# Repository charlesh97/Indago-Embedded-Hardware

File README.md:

# Indago-Embedded-HW

Archived project.

See latest
[PCB](https://gitlab.com/indago-smart-tracker/indago-embedded-hw/-/blob/main/Hardware/v5_Miniature/Main%20Design%20B/Tracker_v5BPCB.pdf),
[Schematic](https://gitlab.com/indago-smart-tracker/indago-embedded-hw/-/blob/main/Hardware/v5_Miniature/Main%20Design%20B/Tracker_v5BSCH.pdf),
[Staged Product Rendering](https://gitlab.com/indago-smart-tracker/indago-embedded-hw/-/blob/main/Renderings/AssetTracker_TestProductMockup.png)

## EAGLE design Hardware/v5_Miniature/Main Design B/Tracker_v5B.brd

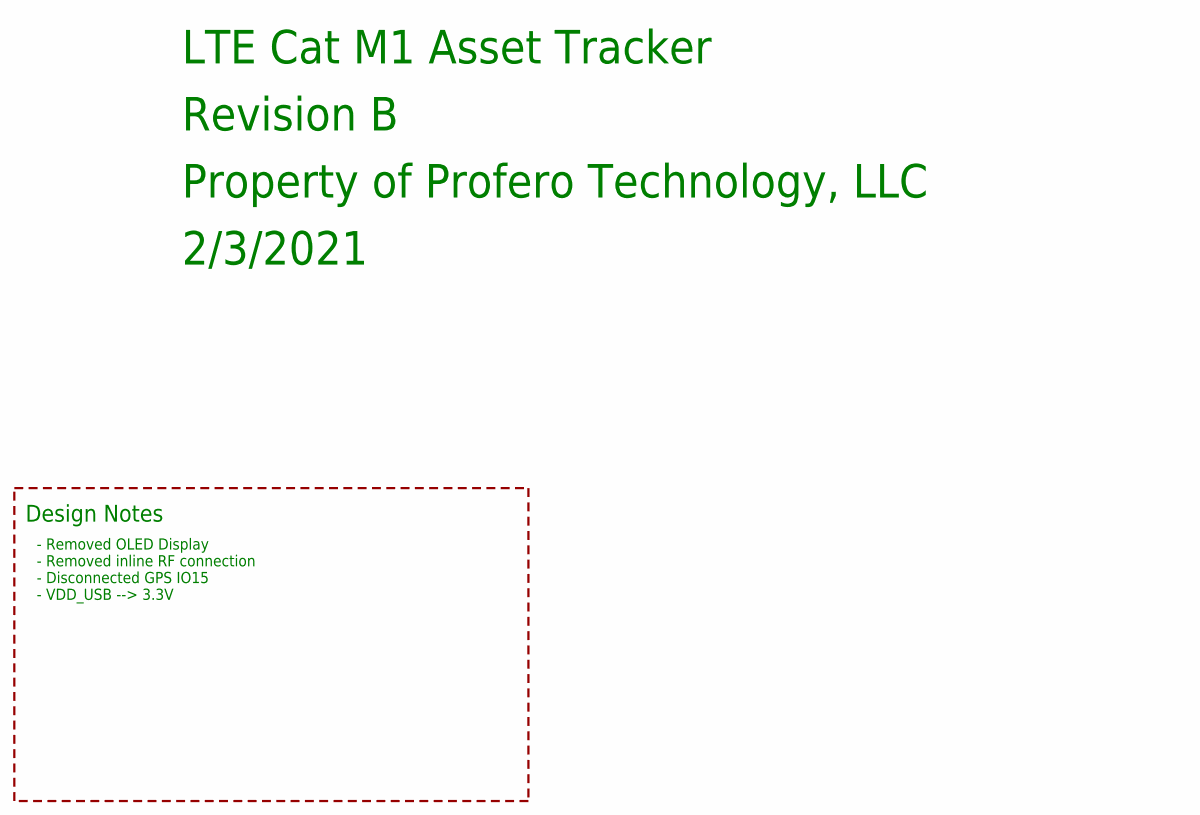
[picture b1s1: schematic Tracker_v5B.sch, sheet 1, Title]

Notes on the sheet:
LTE Cat M1 Asset Tracker
Revision B
Property of Profero Technology, LLC
2/3/2021
Design Notes
- Removed OLED Display - Removed inline RF connection - Disconnected GPS IO15 - VDD_USB --> 3.3V

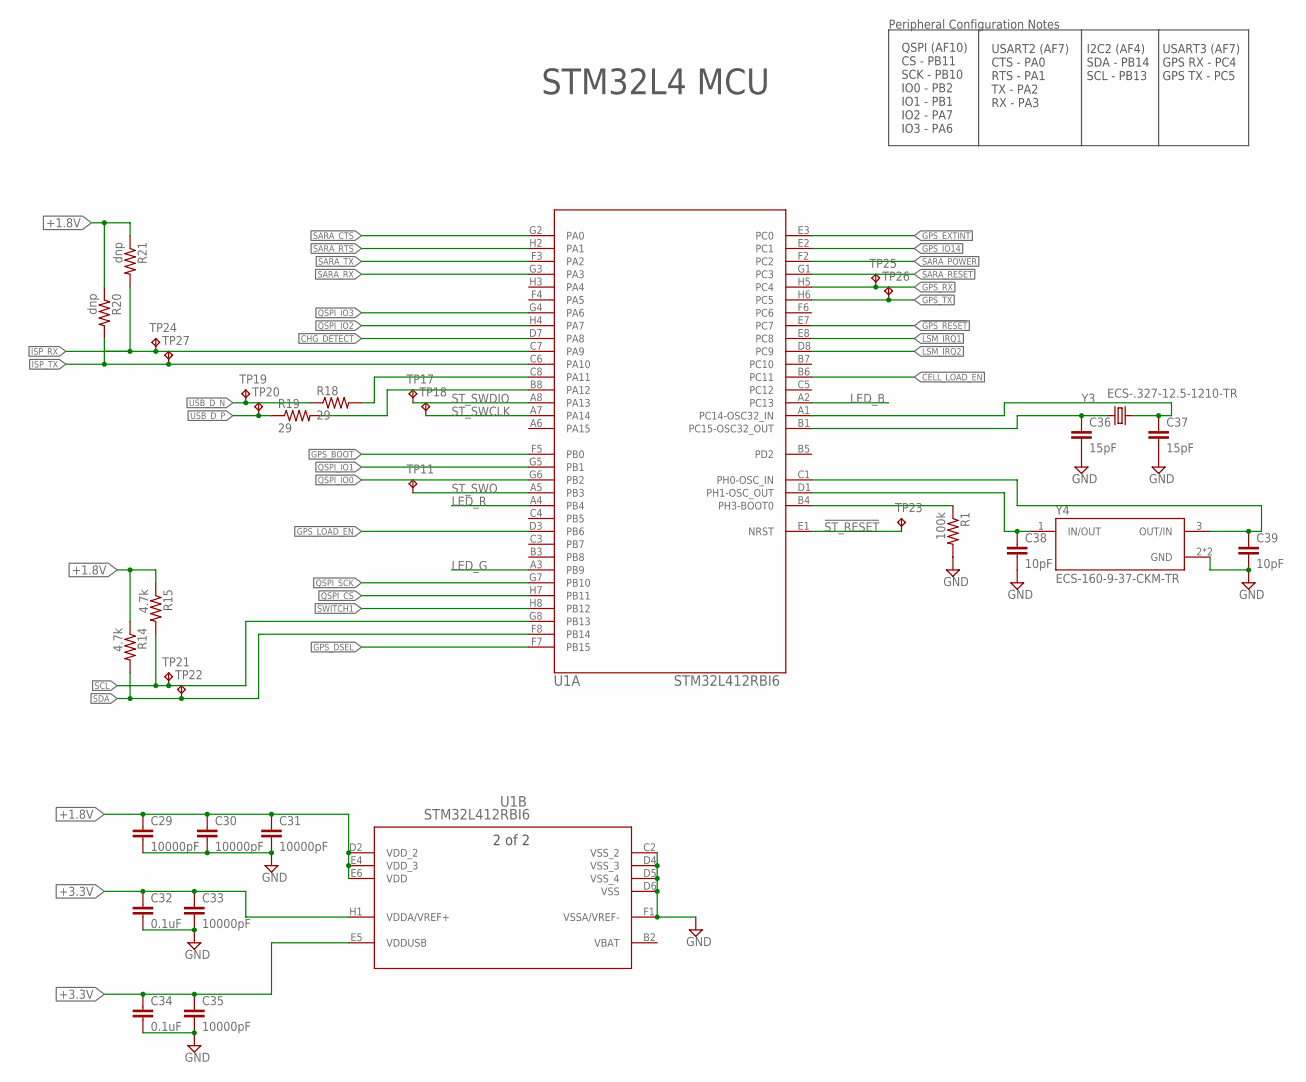
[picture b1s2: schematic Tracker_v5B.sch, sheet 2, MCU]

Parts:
C29, C30, C31, C33, C35: 10000pF; C0201
C32, C34: 0.1uF; C0201
C36, C37: 15pF; C0201
C38, C39: 10pF; C0201
R1: 100k; R0201
R14, R15: 4.7k; R0201
R18, R19: 29; R0201
R20, R21: dnp; R0201
TP11, TP17, TP18, TP19, TP20, TP21, TP22, TP23, TP24, TP25, TP26, TP27: TPTP15R; TP15R
U1: STM32L412RBI6; BGA64C50P8X8_500X500X60N
Y3: ECS-.327-12.5-1210-TR
Y4: ECS-160-9-37-CKM-TR; XTAL_ECS-160-9-37-CKM-TR

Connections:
!GPS_RESET: U1.E7 (PC7); also elsewhere on the board
!SARA_RESET: U1.G1 (PC3); also elsewhere on the board
!ST_RESET: TP23.TP, U1.E1 (NRST)
+1.8V: C29.1, C30.1, C31.1, R14.1, R15.1, R20.1, R21.1, U1.D2 (VDD_2), U1.E4 (VDD_3), U1.E6 (VDD); also elsewhere on the board
+3.3V: C32.1, C33.1, C34.1, C35.1, U1.E5 (VDDUSB), U1.H1 (VDDA/VREF+); also elsewhere on the board
CELL_LOAD_EN: U1.B6 (PC11); also elsewhere on the board
CHG_DETECT: U1.D7 (PA8); also elsewhere on the board
GND: C29.2, C30.2, C31.2, C32.2, C33.2, C34.2, C35.2, C36.2, C37.2, C38.2, C39.2, R1.2, U1.C2 (VSS_2), U1.D4 (VSS_3), U1.D5 (VSS_4), U1.D6 (VSS), U1.F1 (VSSA/VREF-), Y4.2 (GND), Y4.4 (GND); also elsewhere on the board
GPS_BOOT: U1.F5 (PB0); also elsewhere on the board
GPS_DSEL: U1.F7 (PB15); also elsewhere on the board
GPS_EXTINT: U1.E3 (PC0); also elsewhere on the board
GPS_IO14: U1.E2 (PC1); also elsewhere on the board
GPS_LOAD_EN: U1.D3 (PB6); also elsewhere on the board
GPS_RX: TP25.TP, U1.H5 (PC4); also elsewhere on the board
GPS_TX: TP26.TP, U1.H6 (PC5); also elsewhere on the board
ISP_RX: R21.2, TP24.TP, U1.C7 (PA9); also elsewhere on the board
ISP_TX: R20.2, TP27.TP, U1.C6 (PA10); also elsewhere on the board
LED_B: U1.A2 (PC13); also elsewhere on the board
LED_G: U1.A3 (PB9); also elsewhere on the board
LED_R: U1.A4 (PB4); also elsewhere on the board
LSM_IRQ1: U1.E8 (PC8); also elsewhere on the board
LSM_IRQ2: U1.D8 (PC9); also elsewhere on the board
unnamed: R18.2, U1.C8 (PA11)
unnamed: R19.2, U1.B8 (PA12)
unnamed: C36.1, U1.B1 (PC15-OSC32_OUT), Y3.1
unnamed: C37.1, U1.A1 (PC14-OSC32_IN), Y3.2
unnamed: C39.1, U1.C1 (PH0-OSC_IN), Y4.3 (OUT/IN)
unnamed: C38.1, U1.D1 (PH1-OSC_OUT), Y4.1 (IN/OUT)
unnamed: R1.1, U1.B4 (PH3-BOOT0)
QSPI_CS: U1.H7 (PB11); also elsewhere on the board
QSPI_IO0: U1.G6 (PB2); also elsewhere on the board
QSPI_IO1: U1.G5 (PB1); also elsewhere on the board
QSPI_IO2: U1.H4 (PA7); also elsewhere on the board
QSPI_IO3: U1.G4 (PA6); also elsewhere on the board
QSPI_SCK: U1.G7 (PB10); also elsewhere on the board
SARA_CTS: U1.G2 (PA0); also elsewhere on the board
SARA_POWER: U1.F2 (PC2); also elsewhere on the board
SARA_RTS: U1.H2 (PA1); also elsewhere on the board
SARA_RX: U1.G3 (PA3); also elsewhere on the board
SARA_TX: U1.F3 (PA2); also elsewhere on the board
SCL: R15.2, TP21.TP, U1.G8 (PB13); also elsewhere on the board
SDA: R14.2, TP22.TP, U1.F8 (PB14); also elsewhere on the board
ST_SWCLK: TP18.TP, U1.A7 (PA14)
ST_SWDIO: TP17.TP, U1.A8 (PA13)
ST_SWO: TP11.TP, U1.A5 (PB3)
SWITCH1: U1.H8 (PB12); also elsewhere on the board
USB_D_N: R18.1, TP19.TP
USB_D_P: R19.1, TP20.TP
VBAT: U1.B2 (VBAT)

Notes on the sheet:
Peripheral Configuration Notes
STM32L4 MCU
I2C2 (AF4) SDA - PB14 SCL - PB13
QSPI (AF10) CS - PB11 SCK - PB10 IO0 - PB2 IO1 - PB1 IO2 - PA7 IO3 - PA6
USART2 (AF7) CTS - PA0 RTS - PA1 TX - PA2 RX - PA3
USART3 (AF7) GPS RX - PC4 GPS TX - PC5

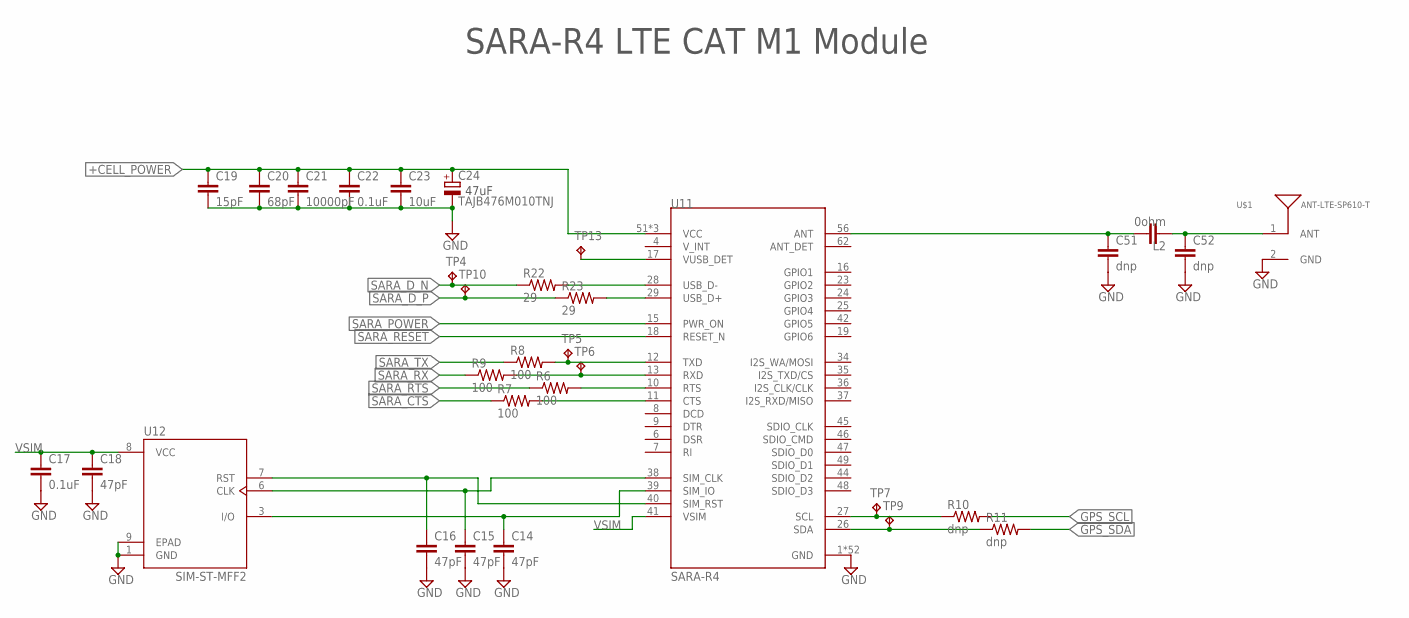
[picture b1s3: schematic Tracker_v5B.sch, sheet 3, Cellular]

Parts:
C14, C15, C16, C18: 47pF; C0201
C17, C22: 0.1uF; C0201
C19: 15pF; C0201
C20: 68pF; C0201
C21: 10000pF; C0201
C23: 10uF; C0603
C24: TAJB476M010TNJ; CAPMP3528X210N
C51, C52: dnp; C0402
L2: 0ohm; C0402
R6, R7, R8, R9: 100; R0201
R10, R11: dnp; R0201
R22, R23: 29; R0201
TP4, TP5, TP6, TP7, TP9, TP10, TP13: TPTP15R; TP15R
U11: SARA-R4
U12: SIM-ST-MFF2; PSON127P500X600X82-9N
U$1: ANT-LTE-SP610-T

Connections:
!SARA_RESET: U11.18 (RESET_N); also elsewhere on the board
+CELL_POWER: C19.1, C20.1, C21.1, C22.1, C23.1, C24.1 (+), U11.51 (VCC), U11.52 (VCC), U11.53 (VCC); also elsewhere on the board
GND: C14.2, C15.2, C16.2, C17.2, C18.2, C19.2, C20.2, C21.2, C22.2, C23.2, C24.2 (-), C51.2, C52.2, U11.1 (GND), U11.3 (GND), U11.5 (GND), U11.14 (GND), U11.20 (GND), U11.21 (GND), U11.22 (GND), U11.30 (GND), U11.32 (GND), U11.43 (GND), U11.50 (GND), U11.54 (GND), U11.55 (GND), U11.57 (GND), U11.58 (GND), U11.59 (GND), U11.60 (GND), U11.61 (GND), U11.63 (GND), U11.64 (GND), U11.65 (GND), U11.66 (GND), U11.67 (GND), U11.68 (GND), U11.69 (GND), U11.70 (GND), U11.71 (GND), U11.72 (GND), U11.73 (GND), U11.74 (GND), U11.75 (GND), U11.76 (GND), U11.77 (GND), U11.78 (GND), U11.79 (GND), U11.80 (GND), U11.81 (GND), U11.82 (GND), U11.83 (GND), U11.84 (GND), U11.85 (GND), U11.86 (GND), U11.87 (GND), U11.88 (GND), U11.89 (GND), U11.90 (GND), U11.91 (GND), U11.92 (GND), U11.93 (GND), U11.94 (GND), U11.95 (GND), U11.96 (GND), U12.1 (GND), U12.9 (EPAD), U$1.2 (GND); also elsewhere on the board
GPS_SCL: R10.2; also elsewhere on the board
GPS_SDA: R11.2; also elsewhere on the board
unnamed: R9.2, TP6.TP, U11.13 (RXD)
unnamed: R8.2, TP5.TP, U11.12 (TXD)
unnamed: R7.2, U11.11 (CTS)
unnamed: R6.2, U11.10 (RTS)
unnamed: C15.1, U11.38 (SIM_CLK), U12.6 (CLK)
unnamed: C16.1, U11.40 (SIM_RST), U12.7 (RST)
unnamed: C51.1, L2.1, U11.56 (ANT)
unnamed: C14.1, U11.39 (SIM_IO), U12.3 (I/O)
unnamed: R10.1, TP7.TP, U11.27 (SCL)
unnamed: R11.1, TP9.TP, U11.26 (SDA)
unnamed: R22.2, U11.28 (USB_D-)
unnamed: R23.2, U11.29 (USB_D+)
unnamed: C52.1, L2.2, U$1.1 (ANT)
unnamed: TP13.TP, U11.17 (VUSB_DET)
SARA_CTS: R7.1; also elsewhere on the board
SARA_D_N: R22.1, TP4.TP
SARA_D_P: R23.1, TP10.TP
SARA_POWER: U11.15 (PWR_ON); also elsewhere on the board
SARA_RTS: R6.1; also elsewhere on the board
SARA_RX: R9.1; also elsewhere on the board
SARA_TX: R8.1; also elsewhere on the board
VSIM: C17.1, C18.1, U11.41 (VSIM), U12.8 (VCC)

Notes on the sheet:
47uF
SARA-R4 LTE CAT M1 Module

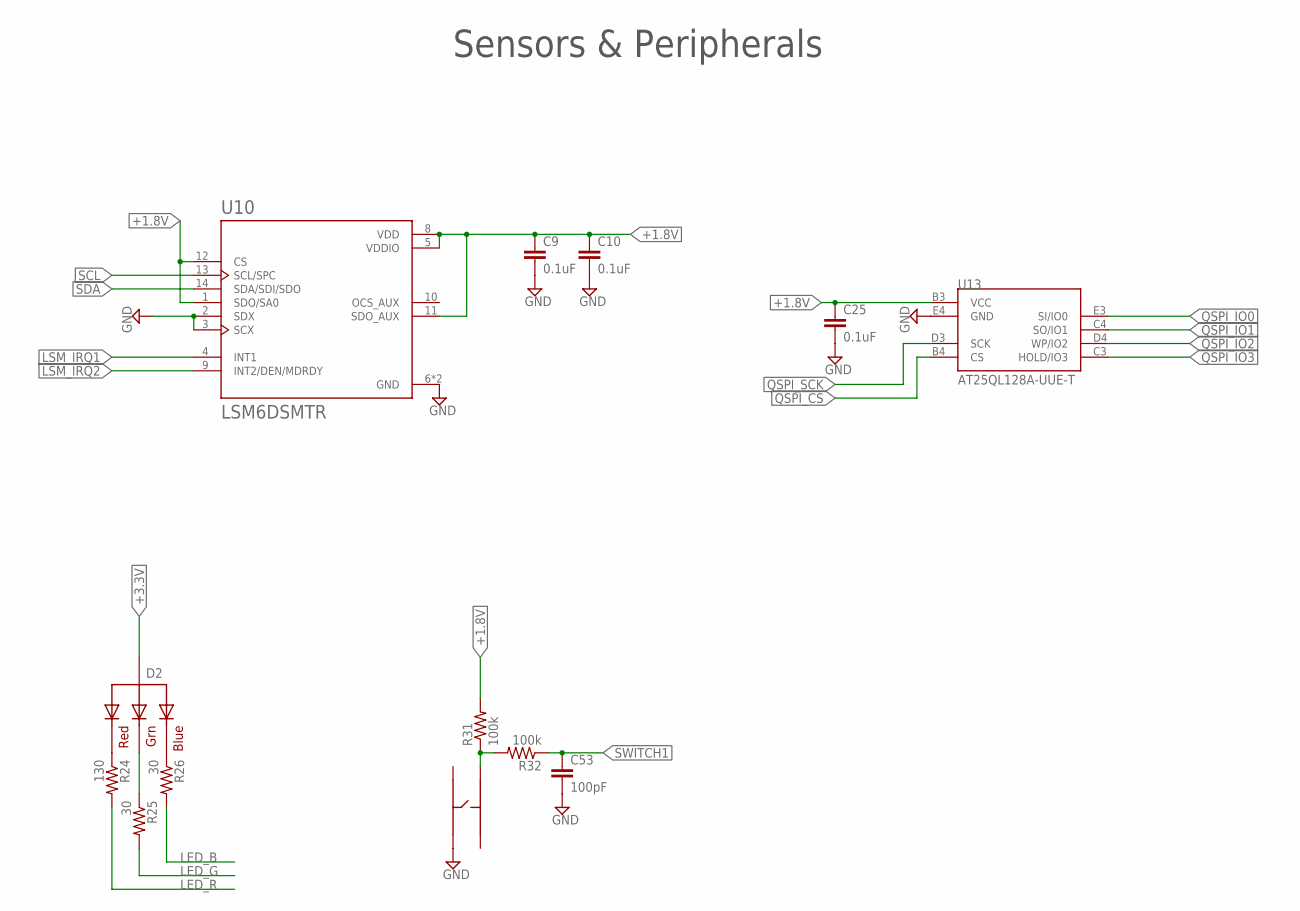
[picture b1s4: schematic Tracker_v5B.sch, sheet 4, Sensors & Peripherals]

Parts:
C9, C10, C25: 0.1uF; C0201
C53: 100pF; C0201
D2: CLMVC-FKA
R24: 130; R0201
R25, R26: 30; R0201
R31, R32: 100k; R0201
S1: EVQ-7PJ; EVQ-7PJ/A
U10: LSM6DSMTR; PQFN50P300X250X86-14N
U13: AT25QL128A-UUE-T; 21-WLCSP

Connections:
+1.8V: C9.1, C10.1, C25.1, R31.2, U10.1 (SDO/SA0), U10.5 (VDDIO), U10.8 (VDD), U10.11 (SDO_AUX), U10.12 (CS), U13.B3 (VCC); also elsewhere on the board
+3.3V: D2.B1 (VCC); also elsewhere on the board
GND: C9.2, C10.2, C25.2, C53.2, S1.P$1, U10.2 (SDX), U10.3 (SCX), U10.6 (GND), U10.7 (GND), U13.E4 (GND); also elsewhere on the board
LED_B: R26.2; also elsewhere on the board
LED_G: R25.2; also elsewhere on the board
LED_R: R24.2; also elsewhere on the board
LSM_IRQ1: U10.4 (INT1); also elsewhere on the board
LSM_IRQ2: U10.9 (INT2/DEN/MDRDY); also elsewhere on the board
unnamed: D2.B4 (RED), R24.1
unnamed: D2.B3 (GREEN), R25.1
unnamed: D2.B2 (BLUE), R26.1
unnamed: R31.1, R32.2, S1.P$4
QSPI_CS: U13.B4 (CS); also elsewhere on the board
QSPI_IO0: U13.E3 (SI/IO0); also elsewhere on the board
QSPI_IO1: U13.C4 (SO/IO1); also elsewhere on the board
QSPI_IO2: U13.D4 (WP/IO2); also elsewhere on the board
QSPI_IO3: U13.C3 (HOLD/IO3); also elsewhere on the board
QSPI_SCK: U13.D3 (SCK); also elsewhere on the board
SCL: U10.13 (SCL/SPC); also elsewhere on the board
SDA: U10.14 (SDA/SDI/SDO); also elsewhere on the board
SWITCH1: C53.1, R32.1; also elsewhere on the board

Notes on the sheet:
Sensors & Peripherals

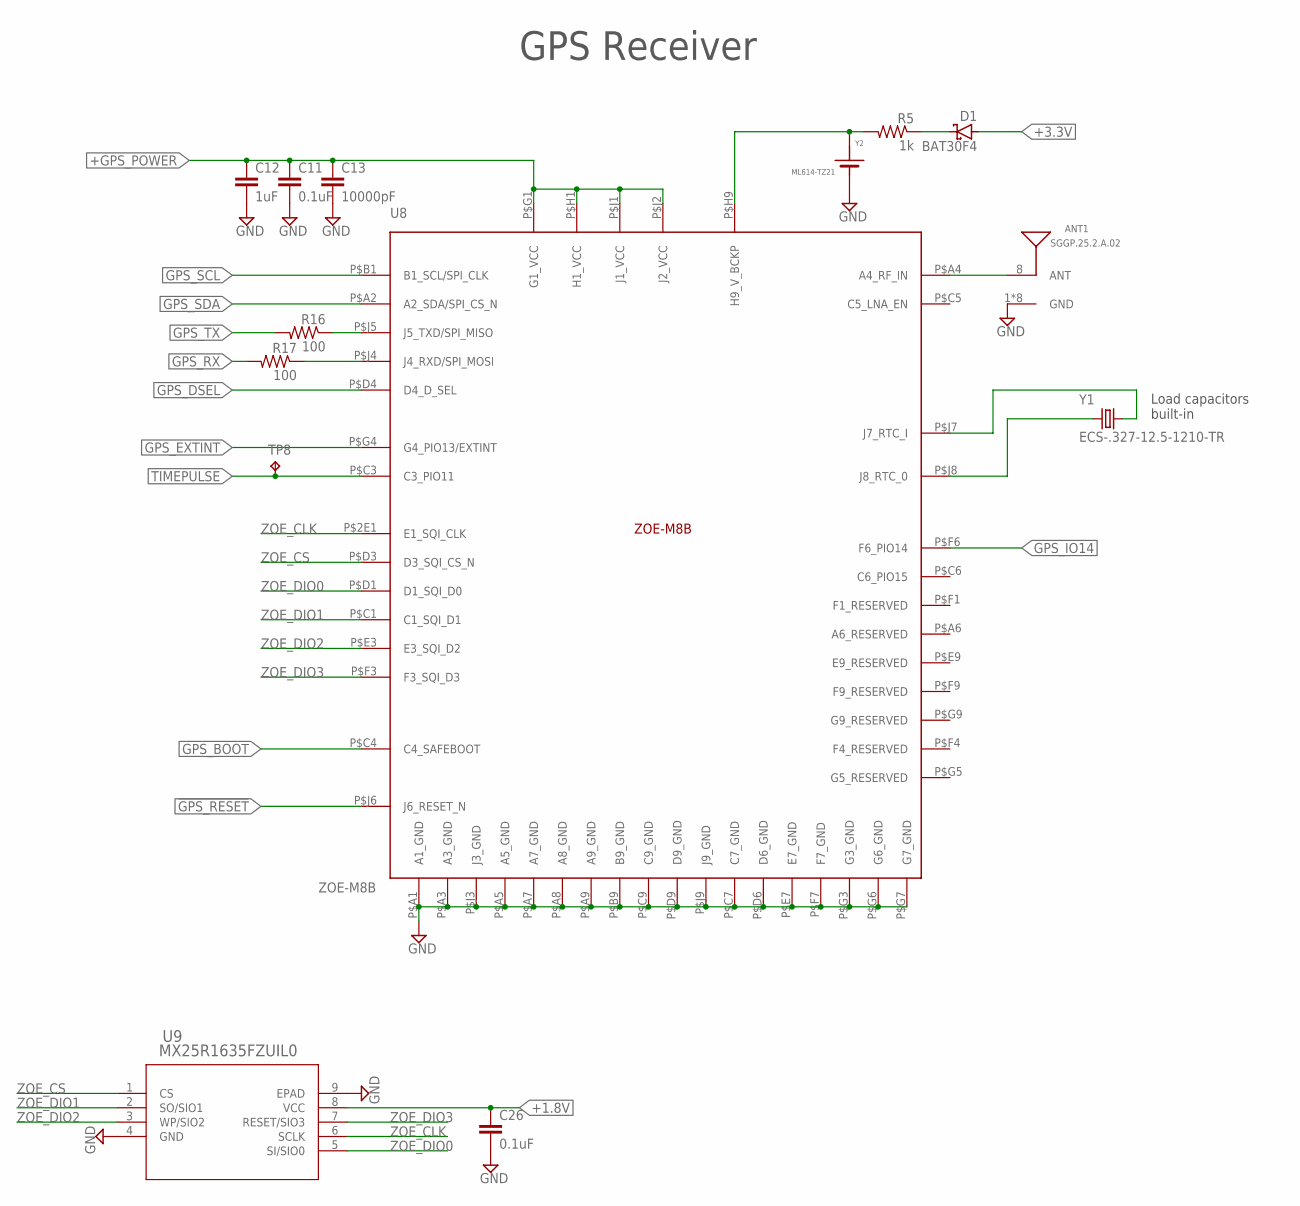
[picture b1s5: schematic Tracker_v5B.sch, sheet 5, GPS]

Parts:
ANT1: SGGP.25.2.A.02
C11, C26: 0.1uF; C0201
C12: 1uF; C0201
C13: 10000pF; C0201
D1: BAT30F4
R5: 1k; R0201
R16, R17: 100; R0201
TP8: TPTP15R; TP15R
U8: ZOE-M8B; ZOE-M8
U9: MX25R1635FZUIL0; USON-8L-2X3X0P6_MAC
Y1: ECS-.327-12.5-1210-TR
Y2: ML614-TZ21

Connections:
!GPS_RESET: U8.P$J6 (J6_RESET_N); also elsewhere on the board
+1.8V: C26.1, U9.8 (VCC); also elsewhere on the board
+3.3V: D1.2 (A); also elsewhere on the board
+GPS_POWER: C11.1, C12.1, C13.1, U8.P$G1 (G1_VCC), U8.P$H1 (H1_VCC), U8.P$J1 (J1_VCC), U8.P$J2 (J2_VCC); also elsewhere on the board
GND: ANT1.1 (GND), ANT1.2 (GND), ANT1.3 (GND), ANT1.4 (GND), ANT1.5 (GND), ANT1.6 (GND), ANT1.7 (GND), ANT1.9 (GND), C11.2, C12.2, C13.2, C26.2, U8.P$A1 (A1_GND), U8.P$A3 (A3_GND), U8.P$A5 (A5_GND), U8.P$A7 (A7_GND), U8.P$A8 (A8_GND), U8.P$A9 (A9_GND), U8.P$B9 (B9_GND), U8.P$C7 (C7_GND), U8.P$C9 (C9_GND), U8.P$D6 (D6_GND), U8.P$D9 (D9_GND), U8.P$E7 (E7_GND), U8.P$F7 (F7_GND), U8.P$G3 (G3_GND), U8.P$G6 (G6_GND), U8.P$G7 (G7_GND), U8.P$J3 (J3_GND), U8.P$J9 (J9_GND), U9.4 (GND), U9.9 (EPAD), Y2.2; also elsewhere on the board
GPS_BOOT: U8.P$C4 (C4_SAFEBOOT); also elsewhere on the board
GPS_DSEL: U8.P$D4 (D4_D_SEL); also elsewhere on the board
GPS_EXTINT: U8.P$G4 (G4_PIO13/EXTINT); also elsewhere on the board
GPS_IO14: U8.P$F6 (F6_PIO14); also elsewhere on the board
GPS_RX: R17.2; also elsewhere on the board
GPS_SCL: U8.P$B1 (B1_SCL/SPI_CLK); also elsewhere on the board
GPS_SDA: U8.P$A2 (A2_SDA/SPI_CS_N); also elsewhere on the board
GPS_TX: R16.2; also elsewhere on the board
unnamed: U8.P$J8 (J8_RTC_0), Y1.1
unnamed: U8.P$J7 (J7_RTC_I), Y1.2
unnamed: D1.1 (C), R5.1
unnamed: R5.2, U8.P$H9 (H9_V_BCKP), Y2.1
unnamed: R16.1, U8.P$J5 (J5_TXD/SPI_MISO)
unnamed: R17.1, U8.P$J4 (J4_RXD/SPI_MOSI)
unnamed: ANT1.8 (ANT), U8.P$A4 (A4_RF_IN)
TIMEPULSE: TP8.TP, U8.P$C3 (C3_PIO11)
ZOE_CLK: U8.P$2E1 (E1_SQI_CLK), U9.6 (SCLK)
ZOE_CS: U8.P$D3 (D3_SQI_CS_N), U9.1 (CS)
ZOE_DIO0: U8.P$D1 (D1_SQI_D0), U9.5 (SI/SIO0)
ZOE_DIO1: U8.P$C1 (C1_SQI_D1), U9.2 (SO/SIO1)
ZOE_DIO2: U8.P$E3 (E3_SQI_D2), U9.3 (WP/SIO2)
ZOE_DIO3: U8.P$F3 (F3_SQI_D3), U9.7 (RESET/SIO3)

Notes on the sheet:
GPS Receiver
Load capacitors built-in

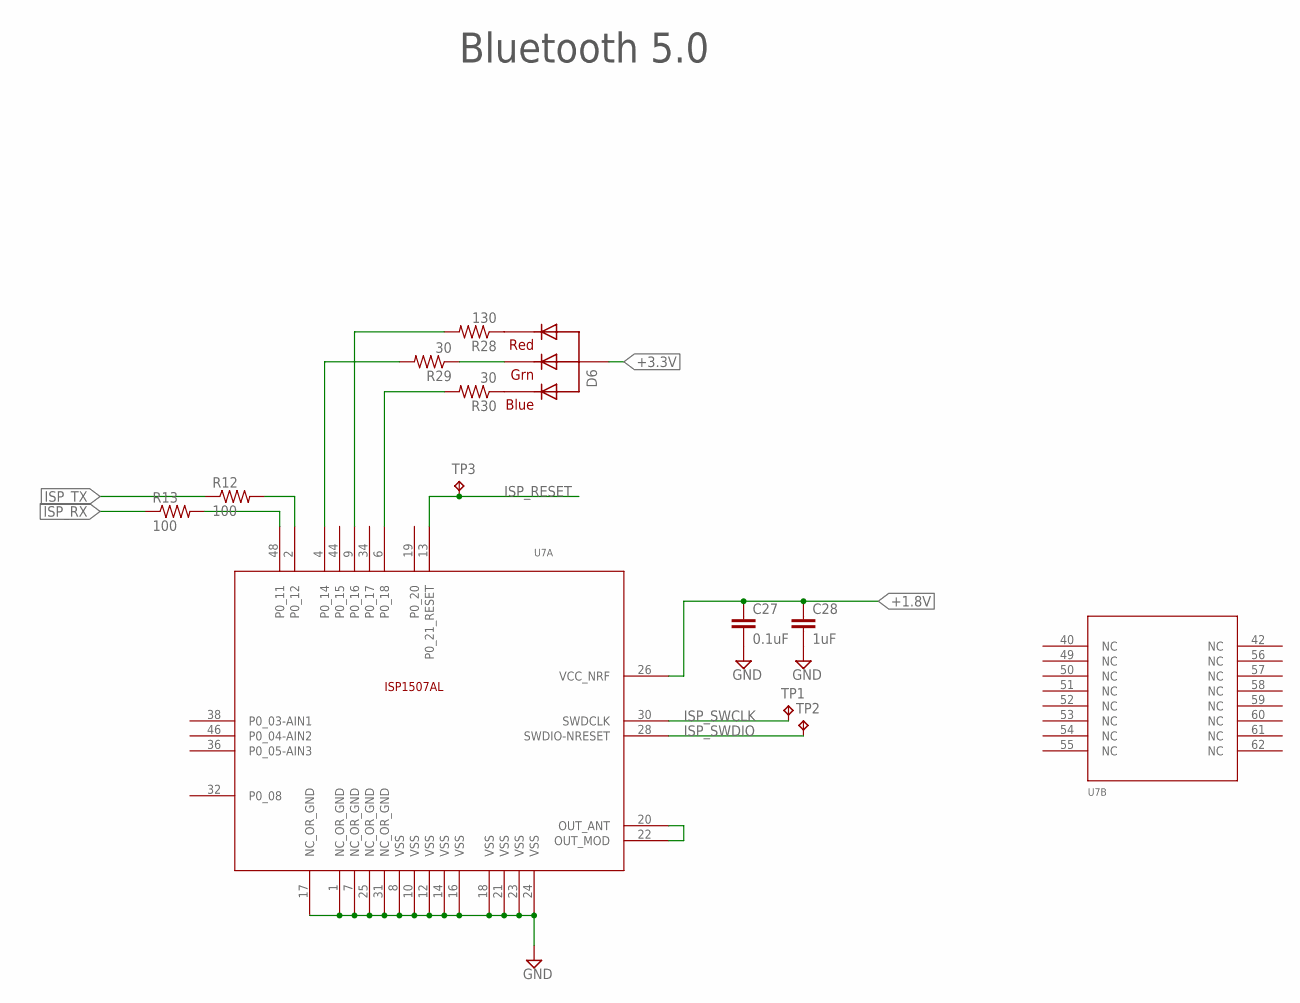
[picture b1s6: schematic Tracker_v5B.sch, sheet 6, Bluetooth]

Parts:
C27: 0.1uF; C0201
C28: 1uF; C0201
D6: CLMVC-FKA
R12, R13: 100; R0201
R28: 130; R0201
R29, R30: 30; R0201
TP1, TP2, TP3: TPTP15R; TP15R
U7: ISP1507ALISP1507AL_ISP1507-AL; ISP1507-AL

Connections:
+1.8V: C27.1, C28.1, U7.26 (VCC_NRF); also elsewhere on the board
+3.3V: D6.B1 (VCC); also elsewhere on the board
GND: C27.2, C28.2, U7.1 (NC_OR_GND), U7.7 (NC_OR_GND), U7.8 (VSS), U7.10 (VSS), U7.12 (VSS), U7.14 (VSS), U7.16 (VSS), U7.17 (NC_OR_GND), U7.18 (VSS), U7.21 (VSS), U7.23 (VSS), U7.24 (VSS), U7.25 (NC_OR_GND), U7.31 (NC_OR_GND); also elsewhere on the board
ISP_RESET: TP3.TP, U7.13 (P0_21_RESET)
ISP_RX: R13.1; also elsewhere on the board
ISP_SWCLK: TP1.TP, U7.30 (SWDCLK)
ISP_SWDIO: TP2.TP, U7.28 (SWDIO-NRESET)
ISP_TX: R12.1; also elsewhere on the board
unnamed: R12.2, U7.2 (P0_12)
unnamed: R13.2, U7.48 (P0_11)
unnamed: U7.20 (OUT_ANT), U7.22 (OUT_MOD)
unnamed: D6.B4 (RED), R28.1
unnamed: D6.B3 (GREEN), R29.1
unnamed: D6.B2 (BLUE), R30.1
unnamed: R30.2, U7.6 (P0_18)
unnamed: R29.2, U7.4 (P0_14)
unnamed: R28.2, U7.9 (P0_16)

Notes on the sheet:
Bluetooth 5.0

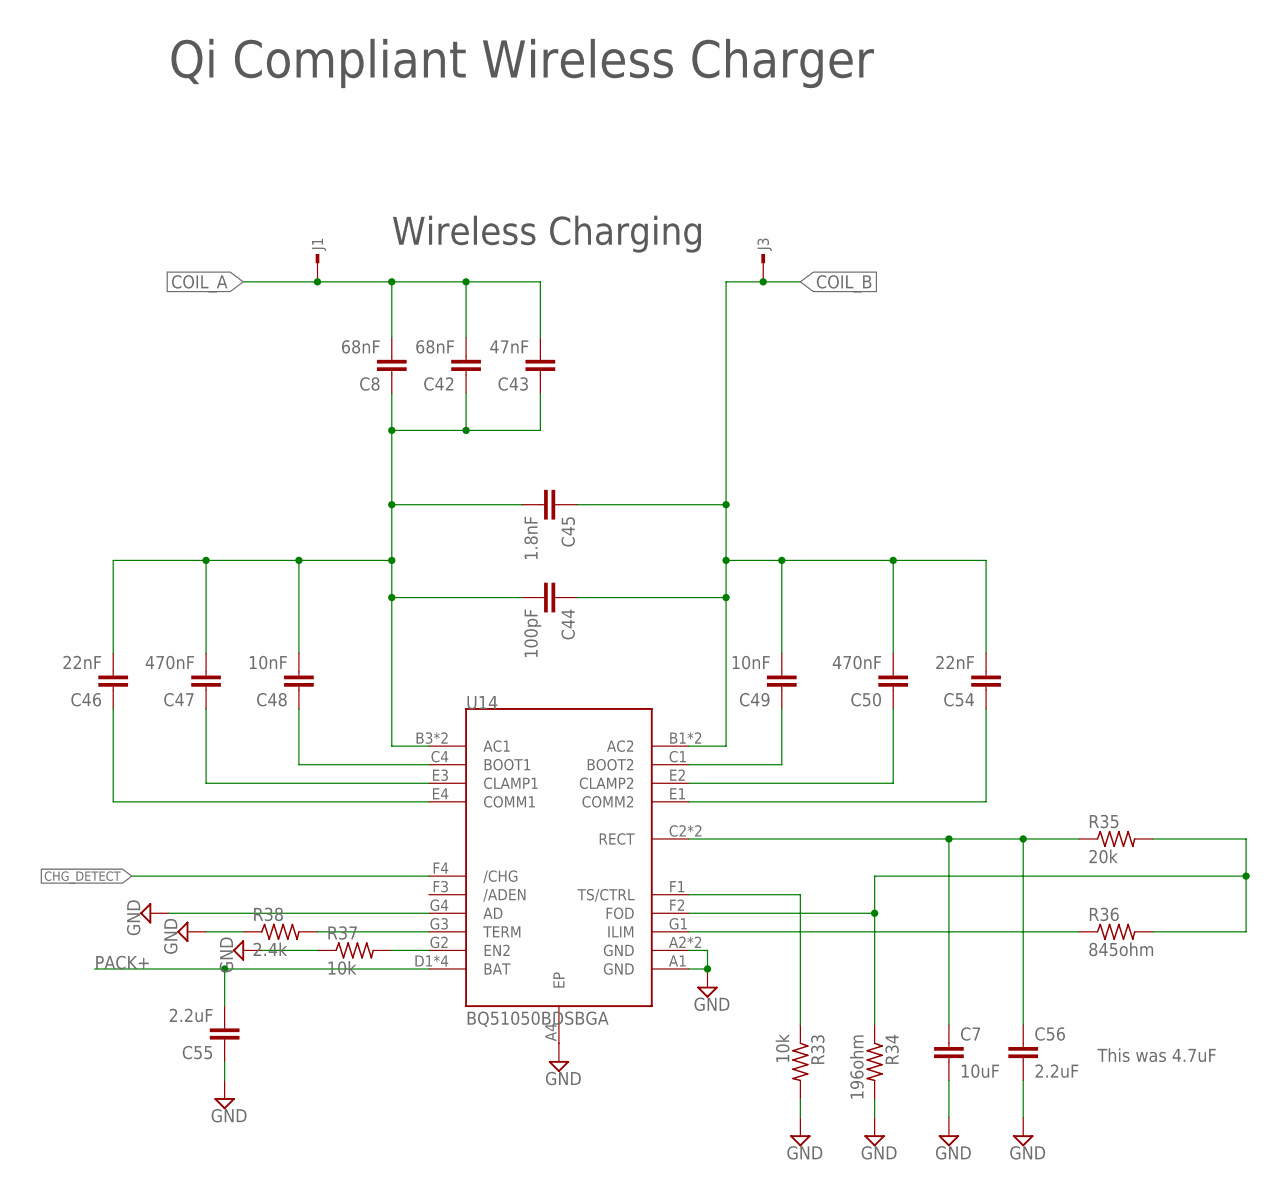
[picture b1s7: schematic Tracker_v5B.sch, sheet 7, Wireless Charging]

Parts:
C7: 10uF; C0402
C8, C42: 68nF; C0402
C43: 47nF; C0402
C44: 100pF; C0402
C45: 1.8nF; C0402
C46, C54: 22nF; C0402
C47, C50: 470nF; C0402
C48, C49: 10nF; C0402
C55, C56: 2.2uF; C0402
J1, J3: SMD_PADPAD_150X75; PAD_150X75
R33, R37: 10k; R0201
R34: 196ohm; R0201
R35: 20k; R0201
R36: 845ohm; R0201
R38: 2.4k; R0201
U14: BQ51050BDSBGA; YFP28

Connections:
CHG_DETECT: U14.F4 (/CHG); also elsewhere on the board
COIL_A: C8.2, C42.2, C43.2, J1.P$1
COIL_B: C44.1, C45.1, C49.2, C50.2, C54.2, J3.P$1, U14.B1 (AC2), U14.B2 (AC2)
GND: C7.2, C55.1, C56.2, R33.2, R34.2, R37.1, R38.1, U14.A1 (GND), U14.A2 (GND), U14.A3 (GND), U14.A4 (EP), U14.G4 (AD); also elsewhere on the board
unnamed: C46.1, U14.E4 (COMM1)
unnamed: C47.1, U14.E3 (CLAMP1)
unnamed: C48.1, U14.C4 (BOOT1)
unnamed: C54.1, U14.E1 (COMM2)
unnamed: C50.1, U14.E2 (CLAMP2)
unnamed: C49.1, U14.C1 (BOOT2)
unnamed: C8.1, C42.1, C43.1, C44.2, C45.2, C46.2, C47.2, C48.2, U14.B3 (AC1), U14.B4 (AC1)
unnamed: R33.1, U14.F1 (TS/CTRL)
unnamed: R34.1, R35.2, R36.2, U14.F2 (FOD)
unnamed: R36.1, U14.G1 (ILIM)
unnamed: C7.1, C56.1, R35.1, U14.C2 (RECT), U14.C3 (RECT)
unnamed: R37.2, U14.G2 (EN2)
unnamed: R38.2, U14.G3 (TERM)
PACK+: C55.2, U14.D1 (BAT), U14.D2 (BAT), U14.D3 (BAT), U14.D4 (BAT); also elsewhere on the board

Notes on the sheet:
Qi Compliant Wireless Charger
This was 4.7uF
Wireless Charging

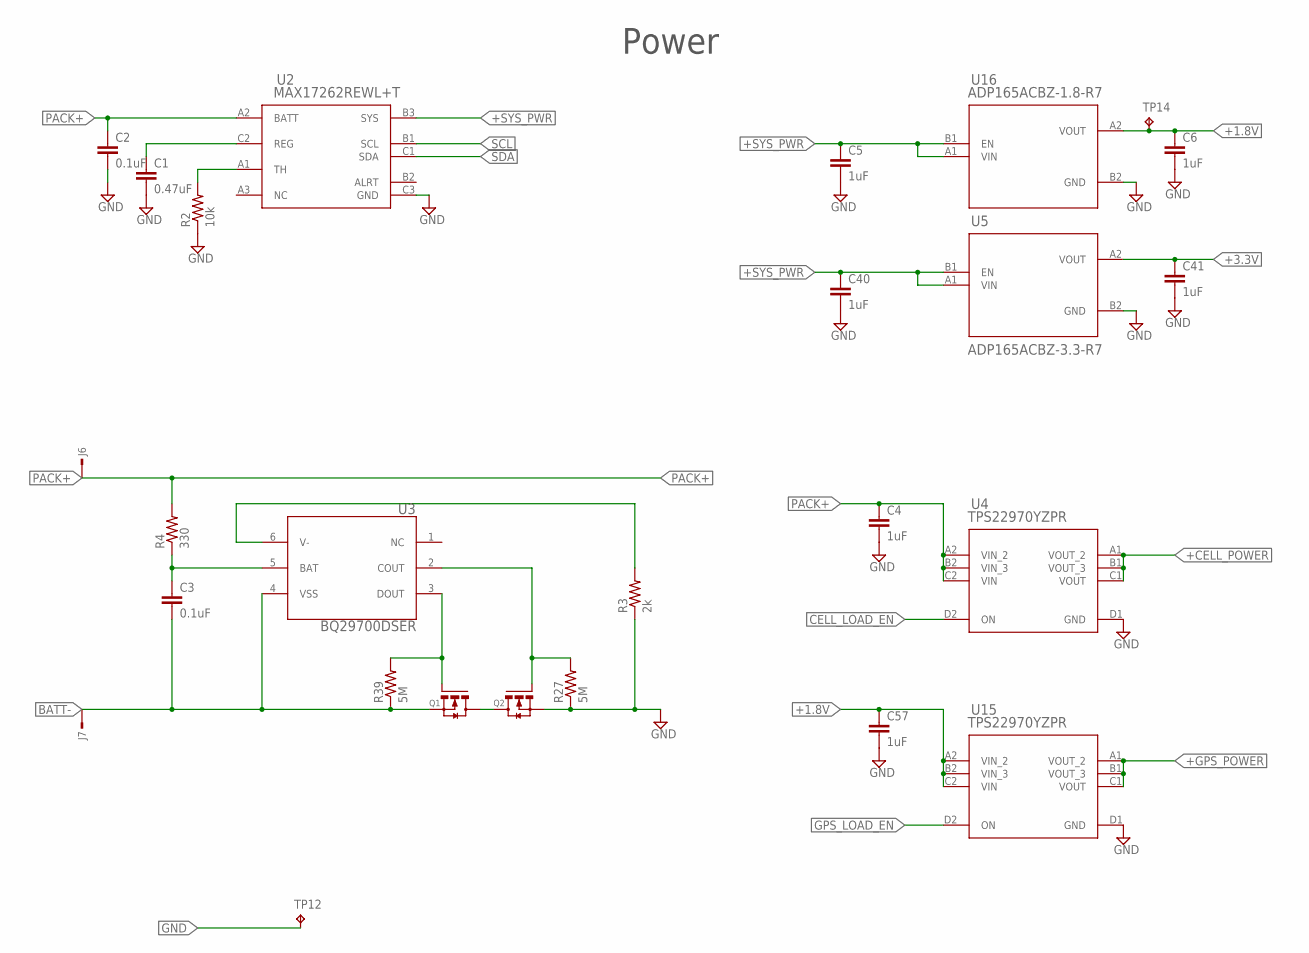
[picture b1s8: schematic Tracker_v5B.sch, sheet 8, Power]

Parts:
C1: 0.47uF; C0201
C2, C3: 0.1uF; C0201
C4, C5, C6, C40, C41, C57: 1uF; C0201
J6, J7: SMD_PADPAD_4MMX5MM; PAD_4MMX5MM
Q1, Q2: CSD13385F5T; YJK3
R2: 10k; R0201
R3: 2k; R0201
R4: 330; R0201
R27, R39: 5M; R0201
TP12, TP14: TPTP15R; TP15R
U2: MAX17262REWL+T; 21-100221A_W91G1+3
U3: BQ29700DSER; DSE0006A
U4, U15: TPS22970YZPR; YZP0008ADCD
U5: ADP165ACBZ-3.3-R7; CB_4_1
U16: ADP165ACBZ-1.8-R7; CB_4_1

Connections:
+1.8V: C6.1, C57.1, TP14.TP, U15.A2 (VIN_2), U15.B2 (VIN_3), U15.C2 (VIN), U16.A2 (VOUT); also elsewhere on the board
+3.3V: C41.1, U5.A2 (VOUT); also elsewhere on the board
+CELL_POWER: U4.A1 (VOUT_2), U4.B1 (VOUT_3), U4.C1 (VOUT); also elsewhere on the board
+GPS_POWER: U15.A1 (VOUT_2), U15.B1 (VOUT_3), U15.C1 (VOUT); also elsewhere on the board
+SYS_PWR: C5.1, C40.1, U2.B3 (SYS), U5.A1 (VIN), U5.B1 (EN), U16.A1 (VIN), U16.B1 (EN)
BATT-: C3.2, J7.P$1, Q1.2 (S), R39.1, U3.4 (VSS)
CELL_LOAD_EN: U4.D2 (ON); also elsewhere on the board
GND: C1.2, C2.2, C4.2, C5.2, C6.2, C40.2, C41.2, C57.2, Q2.2 (S), R2.1, R3.1, R27.1, TP12.TP, U2.C3 (GND), U4.D1 (GND), U5.B2 (GND), U15.D1 (GND), U16.B2 (GND); also elsewhere on the board
GPS_LOAD_EN: U15.D2 (ON); also elsewhere on the board
unnamed: C1.1, U2.C2 (REG)
unnamed: R2.2, U2.A1 (TH)
unnamed: Q1.3 (D), Q2.3 (D)
unnamed: Q1.1 (G), R39.2, U3.3 (DOUT)
unnamed: Q2.1 (G), R27.2, U3.2 (COUT)
unnamed: C3.1, R4.1, U3.5 (BAT)
unnamed: R3.2, U3.6 (V-)
PACK+: C2.1, C4.1, J6.P$1, R4.2, U2.A2 (BATT), U4.A2 (VIN_2), U4.B2 (VIN_3), U4.C2 (VIN); also elsewhere on the board
SCL: U2.B1 (SCL); also elsewhere on the board
SDA: U2.C1 (SDA); also elsewhere on the board

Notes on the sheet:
Power

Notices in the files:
Hardware/v5_Miniature/Main Design B/Tracker_v5B_BOM.csv:
"CSD13385F5T";"CSD13385F5T";"YJK3";"Q1, Q2";"N-Channel 12V 4.3A (Ta) 500mW (Ta) Surface Mount 3-PICOSTAR";"";"";"";"";"";"";"";"Copyright (C) 2018 Accelerated Designs.
X17262REWL+T";"21-100221A_W91G1+3";"U2";"5.2μA 1-Cell Fuel Gauge with ModelGauge m5 EZ and Internal Current Sensing";"";"";"";"";"EMA_Jessica";"";"";"Copyright (C) 2016 Accelerated Designs.
parts and their libraries:
SparkFun-Connectors: Licensing: Creative Commons ShareAlike 4.0 International - https://creativecommons.org/licenses/by-sa/4.0
